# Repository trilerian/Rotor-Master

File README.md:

# Rotor-Master

I have uploaded new Gerbers that have components to put a small load on the output of the sensors.  Also changed the reset resistor to an smb type. 
Need to add the parts to the BOM still
Adds 3 4.7nf 0805 smb capacitors
Adds 4 10k 0805 smb resistors
09/11/2023 - BOM update.  BOM.xlsx is the bom you should use

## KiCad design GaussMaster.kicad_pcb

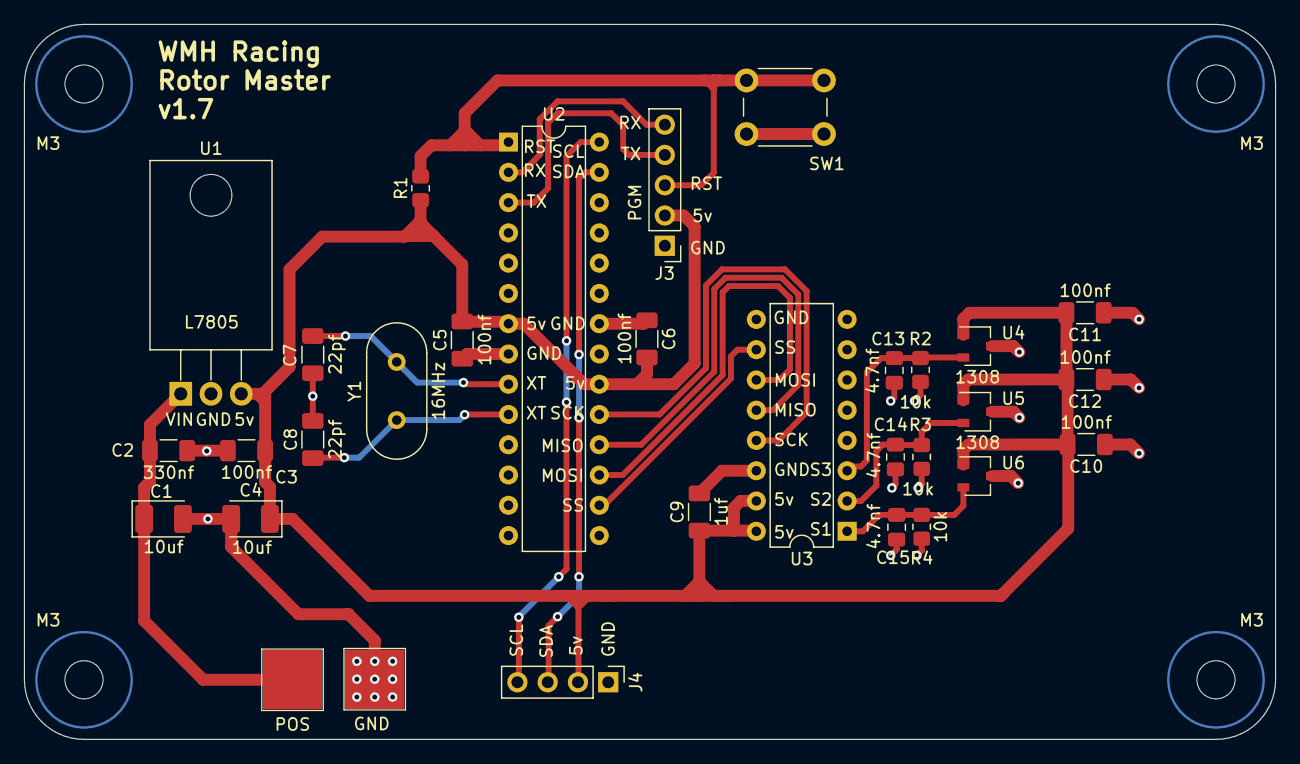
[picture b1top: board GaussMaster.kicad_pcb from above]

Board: 2 copper layers, 105.0 x 60.0 mm, 35 parts (0 on the bottom side), 17 nets.

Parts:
C1, C4: 10uf; CP_EIA-3528-21_Kemet-B_Pad1.50x2.35mm_HandSolder
C2: 330nf; C_1206_3216Metric_Pad1.33x1.80mm_HandSolder
C3, C5, C6, C10, C11, C12: 100nf; C_1206_3216Metric_Pad1.33x1.80mm_HandSolder
C7, C8: 22pf; C_1206_3216Metric_Pad1.33x1.80mm_HandSolder
C9: 1uf; C_1206_3216Metric_Pad1.33x1.80mm_HandSolder
C13, C14, C15: 4.7nf; C_0805_2012Metric_Pad1.18x1.45mm_HandSolder
H1, H2, H3, H4: M3; MountingHole_3.2mm_M3
J1: POS; SolderPad_5x5
J2: GND; SolderPad_5x5
J3: PGM; PinHeader_1x05_P2.54mm_Vertical
J4: I2C; PinHeader_1x04_P2.54mm_Vertical
R1, R2, R3, R4: 10k; R_0805_2012Metric_Pad1.20x1.40mm_HandSolder
SW1: SW_Push_Dual; SW_PUSH_6mm_H7.3mm
U1: L7805; TO-220-3_Horizontal_TabDown
U2: ATmega328P-P; DIP-28_W7.62mm
U3: MCP3208; DIP-16_W7.62mm
U4, U5, U6: 1308; SOT-23W
Y1: 16MHz; Crystal_HC49-4H_Vertical

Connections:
/+5v: C3.1, C4.1, C5.2, C6.2, C9.1, C10.2, C11.2, C12.2, J3.2, J4.2, R1.1, U1.3 (OUT), U2.7 (VCC), U2.20 (AVCC), U3.15 (Vref), U3.16 (Vdd), U4.1 (VCC), U5.1 (VCC), U6.1 (VCC)
/+8.4v: C1.1, C2.1, J1.1, U1.1 (IN)
/MISO: U2.18 (PB4), U3.12 (Dout)
/MOSI: U2.17 (PB3), U3.11 (Din)
/RESET: J3.3, R1.2, SW1.2, U2.1 (~RESET/PC6)
/RX: J3.5, U2.2 (PD0)
/SCK: U2.19 (PB5), U3.13 (CLK)
/SCL: J4.4, U2.28 (PC5)
/SDA: J4.3, U2.27 (PC4)
/SS: U2.16 (PB2), U3.10 (~CS/SHDN)
/TX: J3.4, U2.3 (PD1)
/XTAL1: C7.1, U2.9 (XTAL1/PB6), Y1.2
/XTAL2: C8.1, U2.10 (XTAL2/PB7), Y1.1
GND: C1.2, C2.2, C3.2, C4.2, C5.1, C6.1, C7.2, C8.2, C9.2, C10.1, C11.1, C12.1, C13.2, C14.2, C15.2, J2.1, J3.1, J4.1, R2.2, R3.2, R4.2, SW1.1, U1.2 (GND), U2.8 (GND), U2.22 (GND), U3.9 (DGND), U3.14 (AGND), U4.3 (GND), U5.3 (GND), U6.3 (GND)
SEN1: C15.1, R4.1, U3.1 (CH0), U6.2 (VOUT)
SEN2: C14.1, R3.1, U3.2 (CH1), U5.2 (VOUT)
SEN3: C13.1, R2.1, U3.3 (CH2), U4.2 (VOUT)

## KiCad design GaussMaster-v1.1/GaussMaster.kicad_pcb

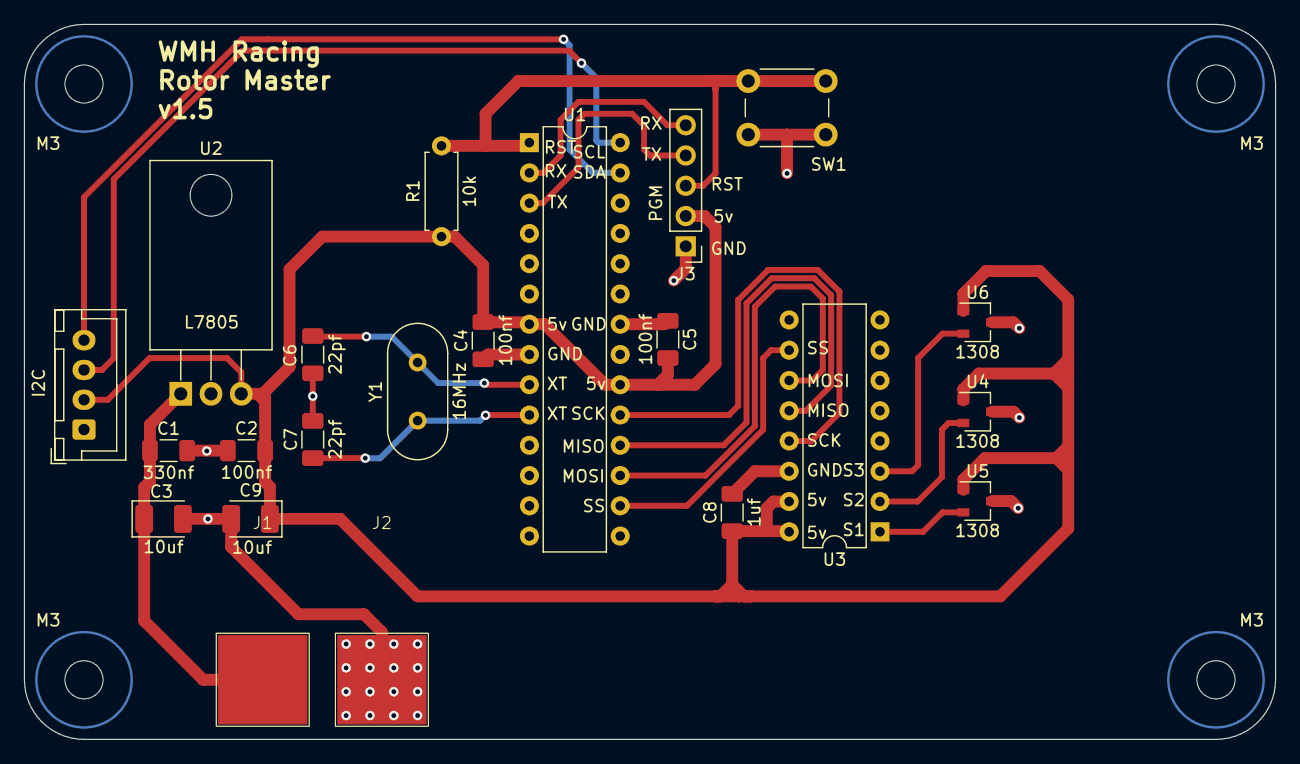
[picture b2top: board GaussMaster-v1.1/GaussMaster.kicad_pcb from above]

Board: 2 copper layers, 105.0 x 60.0 mm, 26 parts (0 on the bottom side), 17 nets.

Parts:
C1: 330nf; C_1206_3216Metric_Pad1.33x1.80mm_HandSolder
C2, C4, C5: 100nf; C_1206_3216Metric_Pad1.33x1.80mm_HandSolder
C3, C9: 10uf; CP_EIA-3528-21_Kemet-B_Pad1.50x2.35mm_HandSolder
C6, C7: 22pf; C_1206_3216Metric_Pad1.33x1.80mm_HandSolder
C8: 1uf; C_1206_3216Metric_Pad1.33x1.80mm_HandSolder
H1, H2, H3, H4: M3; MountingHole_3.2mm_M3
J1: POS; SolderPad_7.5x7.5
J2: GND; SolderPad_7.5x7.5
J3: PGM; PinHeader_1x05_P2.54mm_Vertical
J4: I2C; JST_XH_B4B-XH-A_1x04_P2.50mm_Vertical
R1: 10k; R_Axial_DIN0207_L6.3mm_D2.5mm_P7.62mm_Horizontal
SW1: SW_Push_Dual; SW_PUSH_6mm_H7.3mm
U1: ATmega328P-P; DIP-28_W7.62mm
U2: L7805; TO-220-3_Horizontal_TabDown
U3: MCP3208; DIP-16_W7.62mm
U4, U5, U6: 1308; SOT-23W
Y1: 16MHz; Crystal_HC49-4H_Vertical

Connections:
/+5v: C2.1, C4.2, C5.2, C8.1, C9.1, J3.2, J4.2, R1.1, U1.7 (VCC), U1.20 (AVCC), U2.3 (OUT), U3.15 (Vref), U3.16 (Vdd), U4.1 (VCC), U5.1 (VCC), U6.1 (VCC)
/+8.4v: C1.1, C3.1, J1.1, U2.1 (IN)
/MISO: U1.18 (PB4), U3.12 (Dout)
/MOSI: U1.17 (PB3), U3.11 (Din)
/RESET: J3.3, R1.2, SW1.2, U1.1 (~RESET/PC6)
/RX: J3.5, U1.2 (PD0)
/SCK: U1.19 (PB5), U3.13 (CLK)
/SCL: J4.3, U1.28 (PC5)
/SDA: J4.4, U1.27 (PC4)
/SEN1: U3.1 (CH0), U5.2 (VOUT)
/SEN2: U3.3 (CH2), U6.2 (VOUT)
/SS: U1.16 (PB2), U3.10 (~CS/SHDN)
/TX: J3.4, U1.3 (PD1)
/XTAL1: C6.1, U1.9 (XTAL1/PB6), Y1.2
/XTAL2: C7.1, U1.10 (XTAL2/PB7), Y1.1
GND: C1.2, C2.2, C3.2, C4.1, C5.1, C6.2, C7.2, C8.2, C9.2, J2.1, J3.1, J4.1, SW1.1, U1.8 (GND), U1.22 (GND), U2.2 (GND), U3.9 (DGND), U3.14 (AGND), U4.3 (GND), U5.3 (GND), U6.3 (GND)
unnamed: U3.2 (CH1), U4.2 (VOUT)

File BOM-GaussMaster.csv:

Comment,Designator,Footprint,LCSC
GND,J2,SolderPad_5x5,
POS,J1,SolderPad_5x5,
100nf,C4,C_1206_3216Metric_Pad1.33x1.80mm_HandSolder,
I2C,J4,JST_XH_B4B-XH-A_1x04_P2.50mm_Vertical,
M3,H3,MountingHole_3.2mm_M3,
M3,H2,MountingHole_3.2mm_M3,
ATmega328P-P,U1,DIP-28_W7.62mm,
SW_Push_Dual,SW1,SW_PUSH_6mm_H7.3mm,
16MHz,Y1,Crystal_HC49-4H_Vertical,
100nf,C2,C_1206_3216Metric_Pad1.33x1.80mm_HandSolder,
M3,H1,MountingHole_3.2mm_M3,
10uf,C3,CP_EIA-3528-21_Kemet-B_Pad1.50x2.35mm_HandSolder,
1308,U4,SOT-23W,
1uf,C8,C_1206_3216Metric_Pad1.33x1.80mm_HandSolder,
MCP3208,U3,DIP-16_W7.62mm,
1308,U5,SOT-23W,
22pf,C7,C_1206_3216Metric_Pad1.33x1.80mm_HandSolder,
22pf,C6,C_1206_3216Metric_Pad1.33x1.80mm_HandSolder,
10uf,C9,CP_EIA-3528-21_Kemet-B_Pad1.50x2.35mm_HandSolder,
L7805,U2,TO-220-3_Horizontal_TabDown,
1308,U6,SOT-23W,
100nf,C5,C_1206_3216Metric_Pad1.33x1.80mm_HandSolder,
330nf,C1,C_1206_3216Metric_Pad1.33x1.80mm_HandSolder,
PGM,J3,PinHeader_1x05_P2.54mm_Vertical,
10k,R1,R_Axial_DIN0207_L6.3mm_D2.5mm_P7.62mm_Horizontal,
M3,H4,MountingHole_3.2mm_M3,
